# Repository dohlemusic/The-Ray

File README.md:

# Documentation
A detailed description of the pedal can be found on our blog at https://dohlemusic.ch/dohle-ray-from-a-boost-to-a-heavy-fuzz/

# License
The pedals are published under CC BY-NC-SA 3.0 license https://creativecommons.org/licenses/by-nc-sa/3.0/
In short, this means you can order the electronics from the schematics we publish for yourself and build them yourself, but you can't sell them and you can't publish derivatives of our works unless you mention us as the original author. If you decide to distribute your modification of our product, you can do so only under the same license, which means it can't be used for commerical purposes. We think this is fair to the users and allows them to tinker with our products, without creating a conflict of interest.

# What is the Ray?
When we designed the Ray, we wanted that huge dynamic range and detail of 12AX7 tube you can find in some Fender amps, but in a compact form factor, without building an actual tube into the pedal. We are proud to announce that we did it! We made a unique sounding pedal that offers a very similar tonal characteristics and dynamics to big tube combos, in a tiny package! Pluck the strings delicately, and you will hear the sound of your guitar, nearly unaltered, with that discrete warmth of a tube. Now pluck the strings harder and you can hear a beautiful heavy, yet detailed fuzz of a big old combo!

# What’s inside the Ray?
The pedal is fully analog and sports a subcircuit known as a Fetzer valve. Thanks to a carefully selected JFET transistor (J201) and precisely tuned biasing and capacitors, you can now enjoy a tube sound in a modern form factor. Now, the transistor alone wasn’t enough to push the pedal all the way to fuzz, so we push it with a high quality NE5532 low noise op-amp which gained quite a renown for its sound in audiophile community for its tonal properties and great sound. If you want to know more about the inner workings of this pedal, you can read our blog.

# Why the Ray?
Most fuzz or distortion pedals like the RAT rely on diodes to produce clipping, which in turn results in a very compressed sound that lacks detail and the original tone of your guitar. Ray stands out from the crowd thanks to its ability to produce a very broad dynamic range. This means that when you pluck the strings of your guitar delicately, the tone of your guitar remains almost unaltered, with a little warmth of a tube added. However, if you play the strings harder, you start hearing the warm fuzziness. Even cranked up to the maximum, the now aggressive sound produced by this pedal has very little compression and through the heavy fuzz you can still hear a lot of the original tonal value of your guitar. This is exactly what makes this pedal so unique.

# How to use the Ray
Thanks to the two knobs – V and D (Volume and Drive, respectively), you can control the op-amp gain and JFET gain individually. This means you can create a rich gamut of sounds ranging from pure undistorted boost, through pure JFET boost which has harmonic richness of a vacuum tube, or crank both knobs to the maximum and enjoy a warm fuzz of a big old combo! If you want an even heavier tone, you can toggle the presence switch for that extra fat sound!

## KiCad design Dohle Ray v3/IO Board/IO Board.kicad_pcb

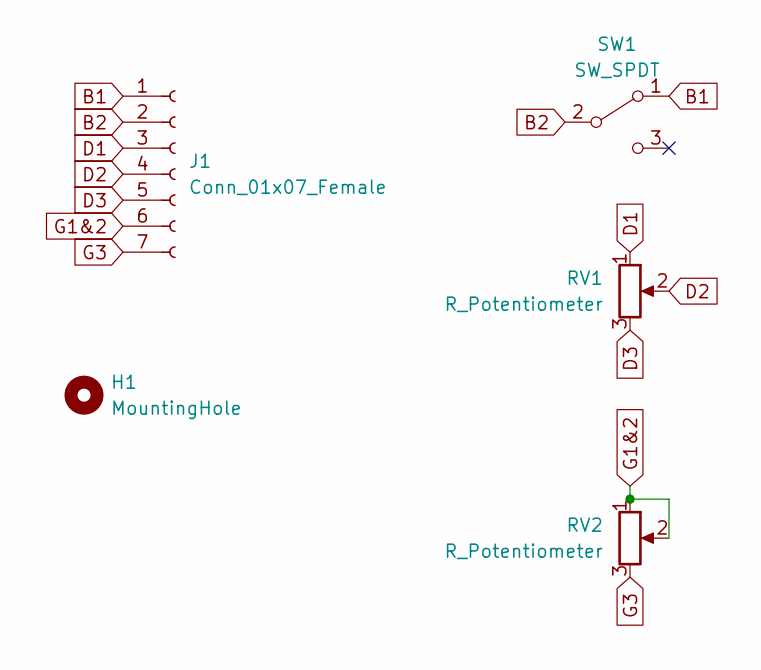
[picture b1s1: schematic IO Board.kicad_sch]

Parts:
H1: MountingHole; MountingHole_2.2mm_M2
J1: Conn_01x07_Female; PinHeader_1x07_P2.54mm_Vertical
RV1, RV2: R_Potentiometer; Vertical big potentiometer
SW1: SW_SPDT; SPDT_fi6mm_footswitch

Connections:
B1: J1.1, SW1.1 (A)
B2: J1.2, SW1.2 (B)
D1: J1.3, RV1.1
D2: J1.4, RV1.2
D3: J1.5, RV1.3
G1&2: J1.6, RV2.1, RV2.2
G3: J1.7, RV2.3

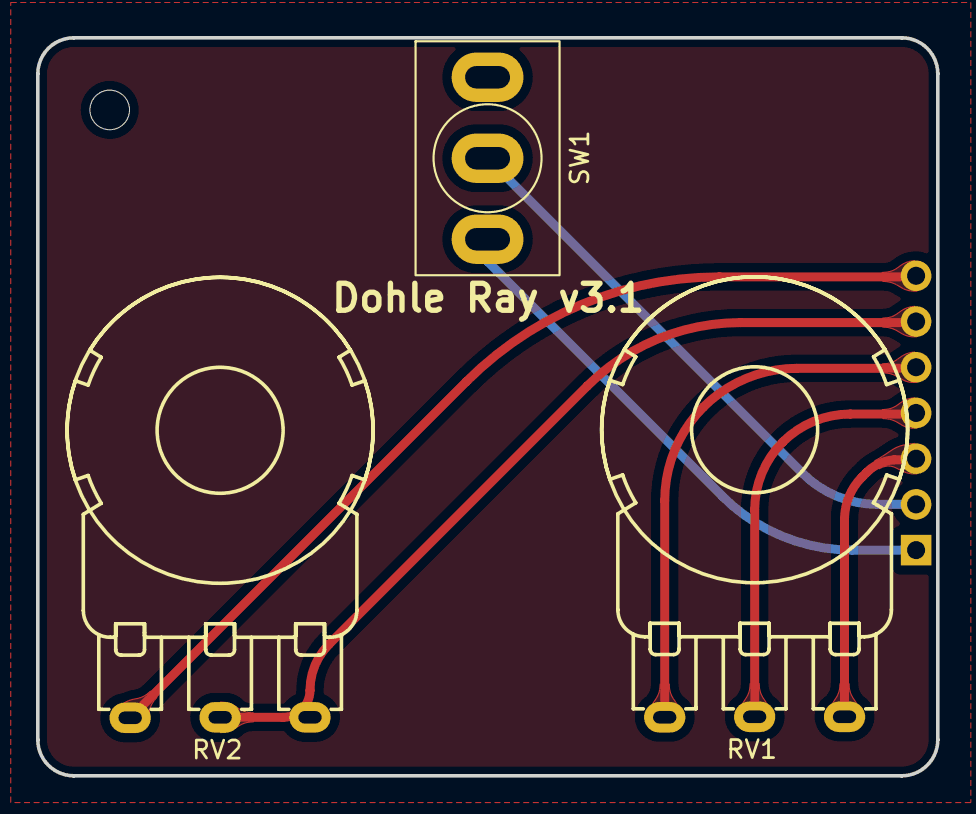
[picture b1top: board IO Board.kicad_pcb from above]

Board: 2 copper layers, 50.0 x 41.0 mm, 5 parts (1 on the bottom side), 7 nets.

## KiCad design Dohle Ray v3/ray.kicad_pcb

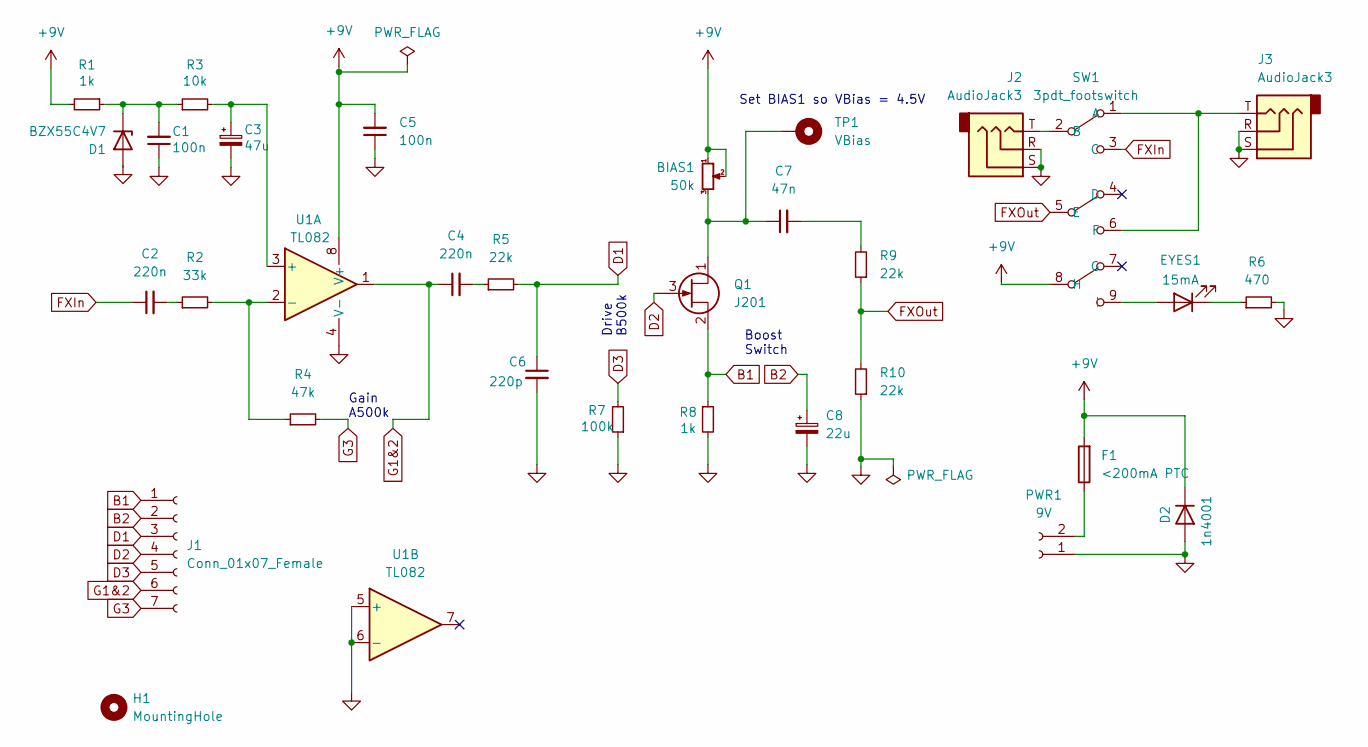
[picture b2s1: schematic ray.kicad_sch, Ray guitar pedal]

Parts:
BIAS1: 50k; Potentiometer_Bourns_3299W_Vertical
C1, C5: 100n; C_Rect_L7.0mm_W4.5mm_P5.00mm
C2, C4: 220n; C_Rect_L7.0mm_W4.5mm_P5.00mm
C3: 47u; CP_Radial_D5.0mm_P2.50mm
C6: 220p; C_Rect_L7.0mm_W2.0mm_P5.00mm
C7: 47n; C_Disc_D5.0mm_W2.5mm_P5.00mm
C8: 22u; CP_Radial_D5.0mm_P2.50mm
D1: BZX55C4V7; D_DO-35_SOD27_P7.62mm_Horizontal
D2: 1n4001; D_DO-15_P12.70mm_Horizontal
EYES1: 15mA; JST_PH_B2B-PH-K_1x02_P2.00mm_Vertical
F1: <200mA PTC; C_Rect_L7.0mm_W4.5mm_P5.00mm
H1: MountingHole; MountingHole_2.2mm_M2
J1: Conn_01x07_Female; PinSocket_1x07_P2.54mm_Vertical
J2, J3: AudioJack3; StereoJackVertical
PWR1: 9V; JST_PH_B2B-PH-K_1x02_P2.00mm_Vertical
Q1: J201; SOT-23_Handsoldering
R1, R8: 1k; R_Axial_DIN0207_L6.3mm_D2.5mm_P10.16mm_Horizontal
R2: 33k; R_Axial_DIN0207_L6.3mm_D2.5mm_P10.16mm_Horizontal
R3: 10k; R_Axial_DIN0207_L6.3mm_D2.5mm_P10.16mm_Horizontal
R4: 47k; R_Axial_DIN0207_L6.3mm_D2.5mm_P10.16mm_Horizontal
R5, R9, R10: 22k; R_Axial_DIN0207_L6.3mm_D2.5mm_P10.16mm_Horizontal
R6: 470; R_Axial_DIN0207_L6.3mm_D2.5mm_P10.16mm_Horizontal
R7: 100k; R_Axial_DIN0207_L6.3mm_D2.5mm_P10.16mm_Horizontal
SW1: 3pdt_footswitch
TP1: VBias; TestPoint_THTPad_1.5x1.5mm_Drill0.7mm
U1: TL082; DIP-8_W7.62mm_Socket_LongPads

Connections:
+9V: BIAS1.1, BIAS1.2, C5.2, D2.1 (K), F1.2, R1.2, SW1.8 (H), U1.8 (V+)
B1: J1.1, Q1.2 (S), R8.1
B2: C8.1, J1.2
D1: C6.1, J1.3, R5.2
D2: J1.4, Q1.3 (G)
D3: J1.5, R7.2
FXIn: C2.1, SW1.3 (C)
FXOut: R9.1, R10.2, SW1.5 (E)
G1&2: C4.1, J1.6, U1.1
G3: J1.7, R4.2
GND: C1.1, C3.2, C5.1, C6.2, C8.2, D1.2 (A), D2.2 (A), J2.R, J2.S, J3.R, J3.S, PWR1.1, R6.2, R7.1, R8.2, R10.1, U1.4 (V-), U1.5 (+), U1.6 (-)
unnamed: BIAS1.3, C7.1, Q1.1 (D), TP1.1
unnamed: C1.2, D1.1 (K), R1.1, R3.1
unnamed: C2.2, R2.1
unnamed: C3.1, R3.2, U1.3 (+)
unnamed: C4.2, R5.1
unnamed: C7.2, R9.2
unnamed: EYES1.1 (K), R6.1
unnamed: EYES1.2 (A), SW1.9 (I)
unnamed: F1.1, PWR1.2
unnamed: J2.T, SW1.2 (B)
unnamed: J3.T, SW1.1 (A), SW1.6 (F)
unnamed: R2.2, R4.1, U1.2 (-)

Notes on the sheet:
Boost Switch
Drive B500k
Set BIAS1 so VBias = 4.5V
Gain A500k

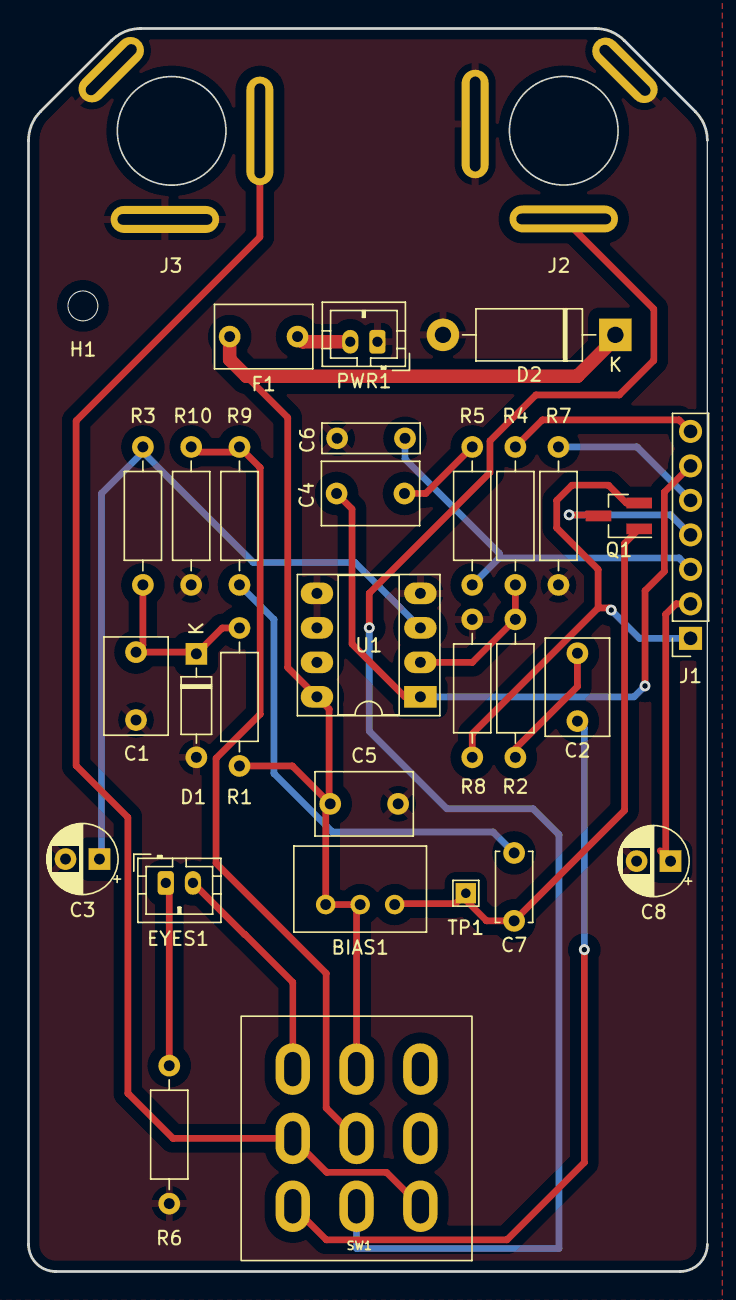
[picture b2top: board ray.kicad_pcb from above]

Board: 2 copper layers, 50.0 x 91.6 mm, 32 parts (0 on the bottom side), 23 nets.

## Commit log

2022-12-03 Add ray pedals
2022-12-03 Add license information
2022-12-03 Update version and fix faulty jack wiring
2022-12-03 Export to jlcpcb
2022-12-12 Prepare fabrication data
2023-06-22 Update resistor values
2023-07-09 Update resistor values to have unity gain at 0% volume and gain knob, update PCB revision
